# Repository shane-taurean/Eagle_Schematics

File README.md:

Eagle_Schematics
================

A collection of schematics and PCB designs

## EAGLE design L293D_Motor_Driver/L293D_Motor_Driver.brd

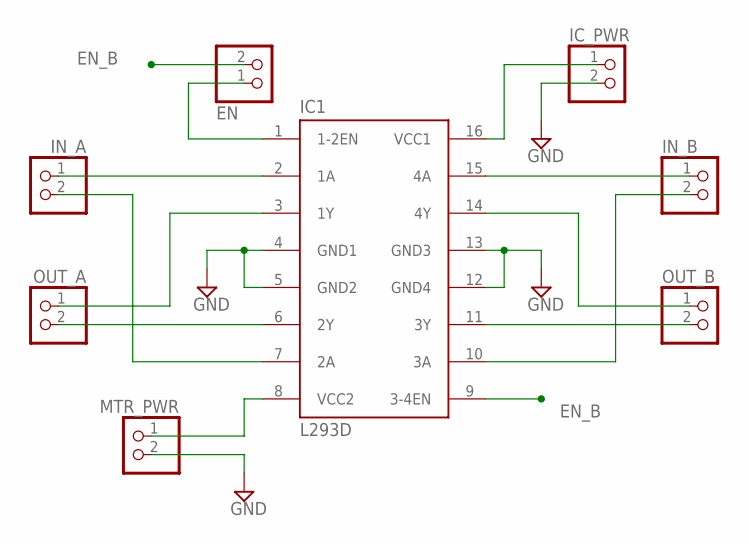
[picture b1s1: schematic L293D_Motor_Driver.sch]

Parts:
EN: PINHD-1X2; 1X02
IC1: L293D; DIL16
IC_PWR: PINHD-1X2; 1X02
IN_A: PINHD-1X2; 1X02
IN_B: PINHD-1X2; 1X02
MTR_PWR: PINHD-1X2; 1X02
OUT_A: PINHD-1X2; 1X02
OUT_B: PINHD-1X2; 1X02

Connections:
1A: IC1.2 (1A), IN_A.1
1Y: IC1.3 (1Y), OUT_A.1
2A: IC1.7 (2A), IN_A.2
2Y: IC1.6 (2Y), OUT_A.2
3A: IC1.10 (3A), IN_B.2
3Y: IC1.11 (3Y), OUT_B.2
4A: IC1.15 (4A), IN_B.1
4Y: IC1.14 (4Y), OUT_B.1
EN_A: EN.1, IC1.1 (1-2EN)
EN_B: EN.2, IC1.9 (3-4EN)
GND: IC1.4 (GND1), IC1.5 (GND2), IC1.12 (GND4), IC1.13 (GND3), IC_PWR.2, MTR_PWR.2
unnamed: IC1.16 (VCC1), IC_PWR.1
unnamed: IC1.8 (VCC2), MTR_PWR.1

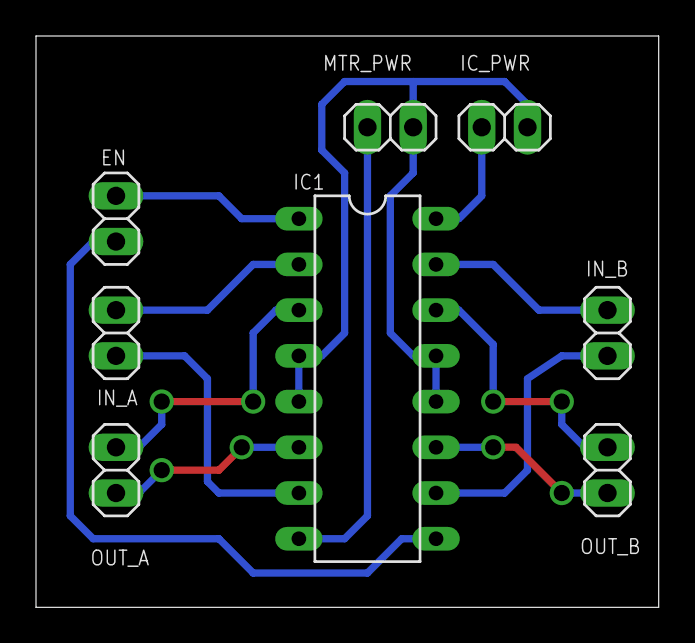
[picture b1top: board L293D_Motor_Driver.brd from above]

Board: 2 copper layers, 34.6 x 31.7 mm, 8 parts (0 on the bottom side), 13 nets.

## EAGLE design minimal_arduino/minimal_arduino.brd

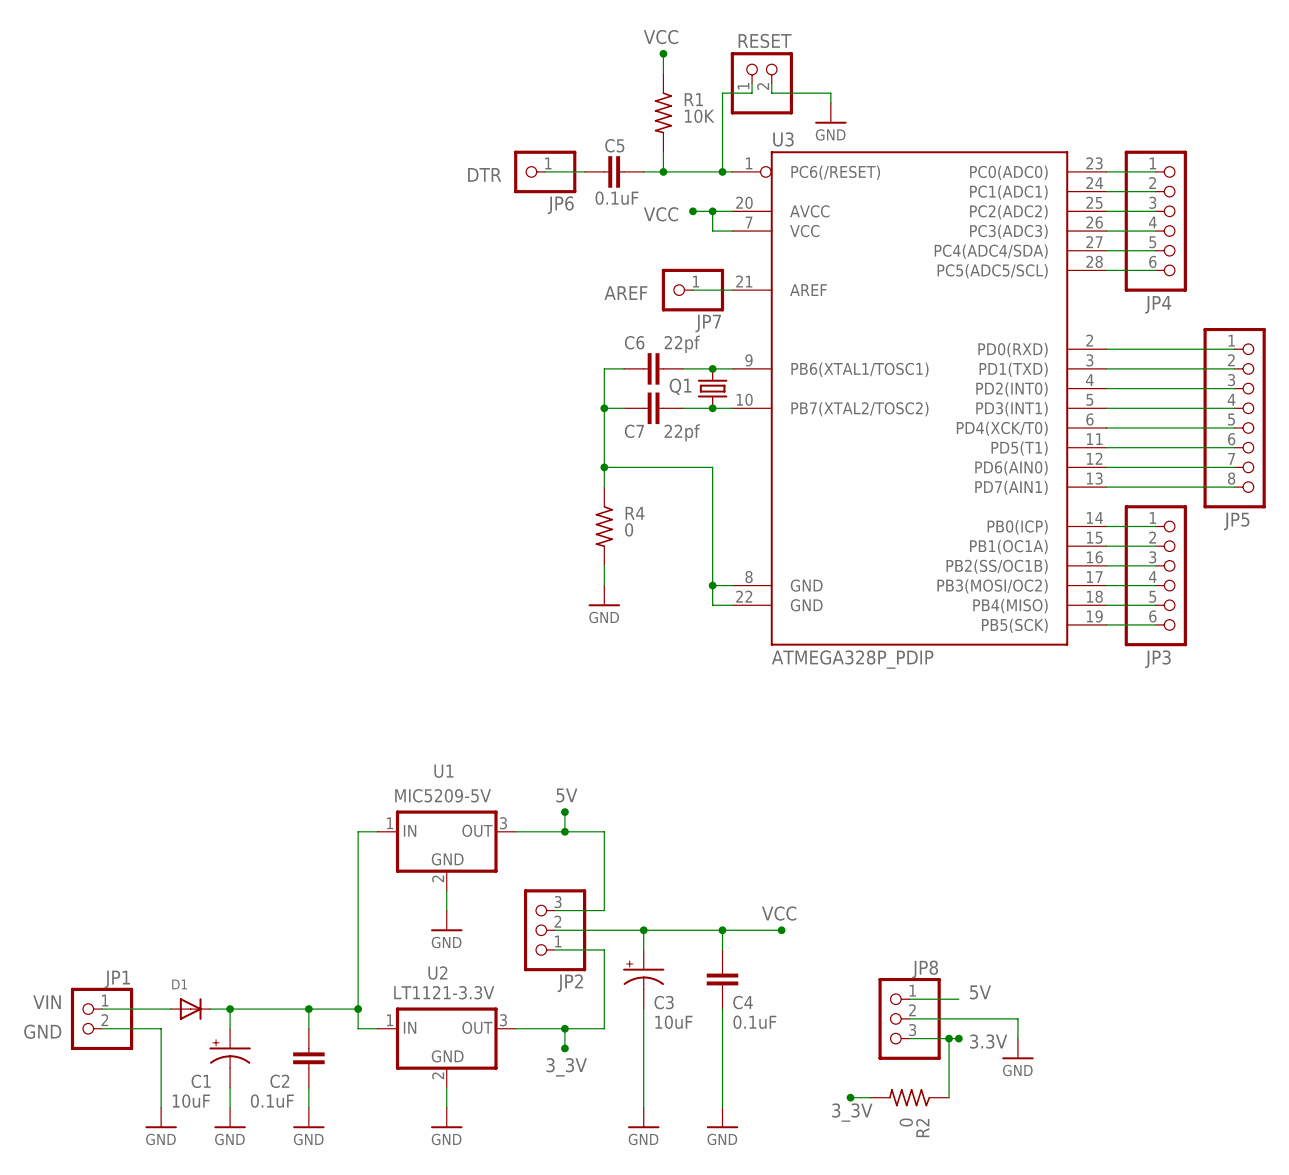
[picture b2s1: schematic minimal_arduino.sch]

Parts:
C1, C3: 10uF; CT3528
C2, C4, C5: 0.1uF; CT3216
C6, C7: 22pf; CT3216
D1: DIODESMA; SMADIODE
JP1: PINHD-1X2; 1X02
JP2, JP8: PINHD-1X3; 1X03
JP3, JP4: PINHD-1X6; 1X06
JP5: PINHD-1X8; 1X08
JP6, JP7: PINHD-1X1; 1X01
Q1: CRYSTALHC18U-V; HC18U-V
R1: 10K; M1406
R2, R4: 0; M1406
RESET: PINHD-1X2; 1X02
U1: MIC5209-5V; SOT223_LT
U2: LT1121-3.3V; SOT223_LT
U3: ATMEGA328P_PDIP; DIL28-3

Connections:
3.3V: JP8.3, R2.1
3_3V: JP2.1, R2.2, U2.3 (VO)
5V: JP2.3, JP8.1, U1.3 (VO)
AREF: JP7.1, U3.21 (AREF)
DTR: C5.+ (1), JP6.1
GND: C1.-, C2.- (2), C3.-, C4.- (2), JP1.2, JP8.2, R4.2, RESET.2, U1.2 (GND), U2.2 (GND)
unnamed: C5.- (2), R1.2, RESET.1, U3.1 (PC6(/RESET))
unnamed: C6.+ (1), C7.+ (1), R4.1, U3.8 (GND), U3.22 (GND)
unnamed: C6.- (2), Q1.2, U3.9 (PB6(XTAL1/TOSC1))
unnamed: C7.- (2), Q1.1, U3.10 (PB7(XTAL2/TOSC2))
unnamed: JP3.1, U3.14 (PB0(ICP))
unnamed: JP3.2, U3.15 (PB1(OC1A))
unnamed: JP3.3, U3.16 (PB2(SS/OC1B))
unnamed: JP3.4, U3.17 (PB3(MOSI/OC2))
unnamed: JP3.5, U3.18 (PB4(MISO))
unnamed: JP3.6, U3.19 (PB5(SCK))
unnamed: JP4.6, U3.28 (PC5(ADC5/SCL))
unnamed: JP4.5, U3.27 (PC4(ADC4/SDA))
unnamed: JP4.4, U3.26 (PC3(ADC3))
unnamed: JP4.3, U3.25 (PC2(ADC2))
unnamed: JP4.2, U3.24 (PC1(ADC1))
unnamed: JP4.1, U3.23 (PC0(ADC0))
unnamed: JP5.1, U3.2 (PD0(RXD))
unnamed: JP5.2, U3.3 (PD1(TXD))
unnamed: JP5.3, U3.4 (PD2(INT0))
unnamed: JP5.4, U3.5 (PD3(INT1))
unnamed: JP5.5, U3.6 (PD4(XCK/T0))
unnamed: JP5.6, U3.11 (PD5(T1))
unnamed: JP5.7, U3.12 (PD6(AIN0))
unnamed: JP5.8, U3.13 (PD7(AIN1))
VCC: C3.+, C4.+ (1), JP2.2, R1.1, U3.7 (VCC), U3.20 (AVCC)
VIN: D1.A, JP1.1
V_IN: C1.+, C2.+ (1), D1.C, U1.1 (VI), U2.1 (VI)

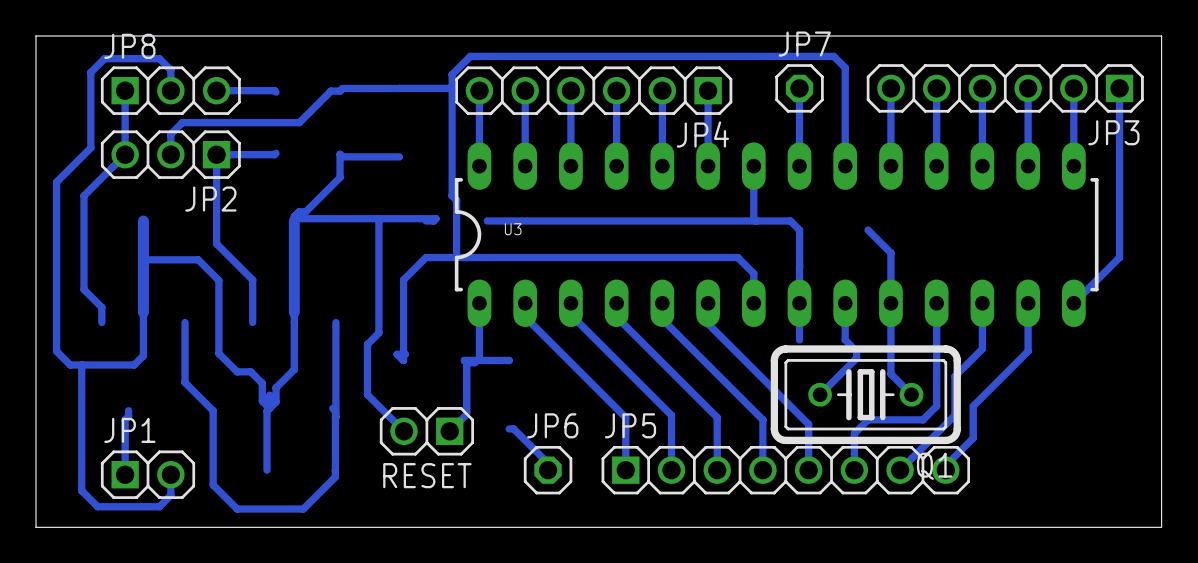
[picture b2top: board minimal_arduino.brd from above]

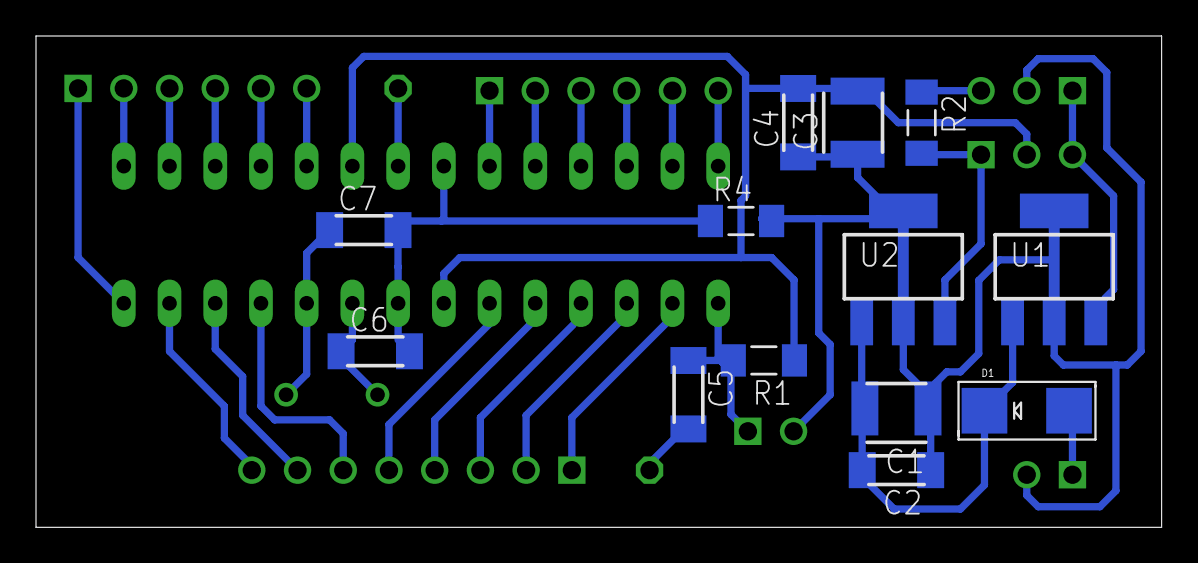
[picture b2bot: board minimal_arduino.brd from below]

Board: 2 copper layers, 62.5 x 27.3 mm, 24 parts (13 on the bottom side), 33 nets.

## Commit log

2014-04-29 Added L293 Motor Driver Board
2014-04-29 added minimal arduino

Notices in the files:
parts and their libraries:
SparkFun-DigitalIC: Licensing: CC v3.0 Share-Alike You are welcome to use this library for commercial purposes.
